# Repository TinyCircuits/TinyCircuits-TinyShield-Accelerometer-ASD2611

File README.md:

# TinyCircuits TinyShield Accelerometer Board
# ASD2611 Rev1

These are the design files for the TinyCircuits ASD2611 Rev 1 PCB.  This is a TinyShield board (Square Version, 20mm x 20mm, or Circular 20mm diameter) that has a Bosch BMA250 accelerometer, local power supply and level shifters to connect between the TinyDuino and the accelerometer. 

Format is in Cadsoft Eagle format - Eagle version 6.2 was used for the original design.

For more infomation on this, check out the product page at Tiny-Circuits.com:  https://tinycircuits.com/collections/sensors/products/accelerometer-tinyshield 

# License:

Design by TinyCircuits.
All design files are released under the Creative Commons Attribution Share-Alike 3.0 License, see the following link for details: http://creativecommons.org/licenses/by-sa/3.0

All text above must be included in any redistribution or derived design

This project uses designs and concepts developed as part of the Arduino project and the LilyPad project.  The TinyCircuits design files themselves (schematics, PCB and libraries) are not directly derived from these works' design files and have been created new, however the concepts and basic architecture behind the TinyDuino and TinyLily products are derived and we thank the hard work of the organizations below for their contributions to open-source hardware:
  
Original Arduino Uno Design by Team Arduino

LilyPad Arduino Design by Leah Buechley and Sparkfun Electronics

Please support the open-source hardware community

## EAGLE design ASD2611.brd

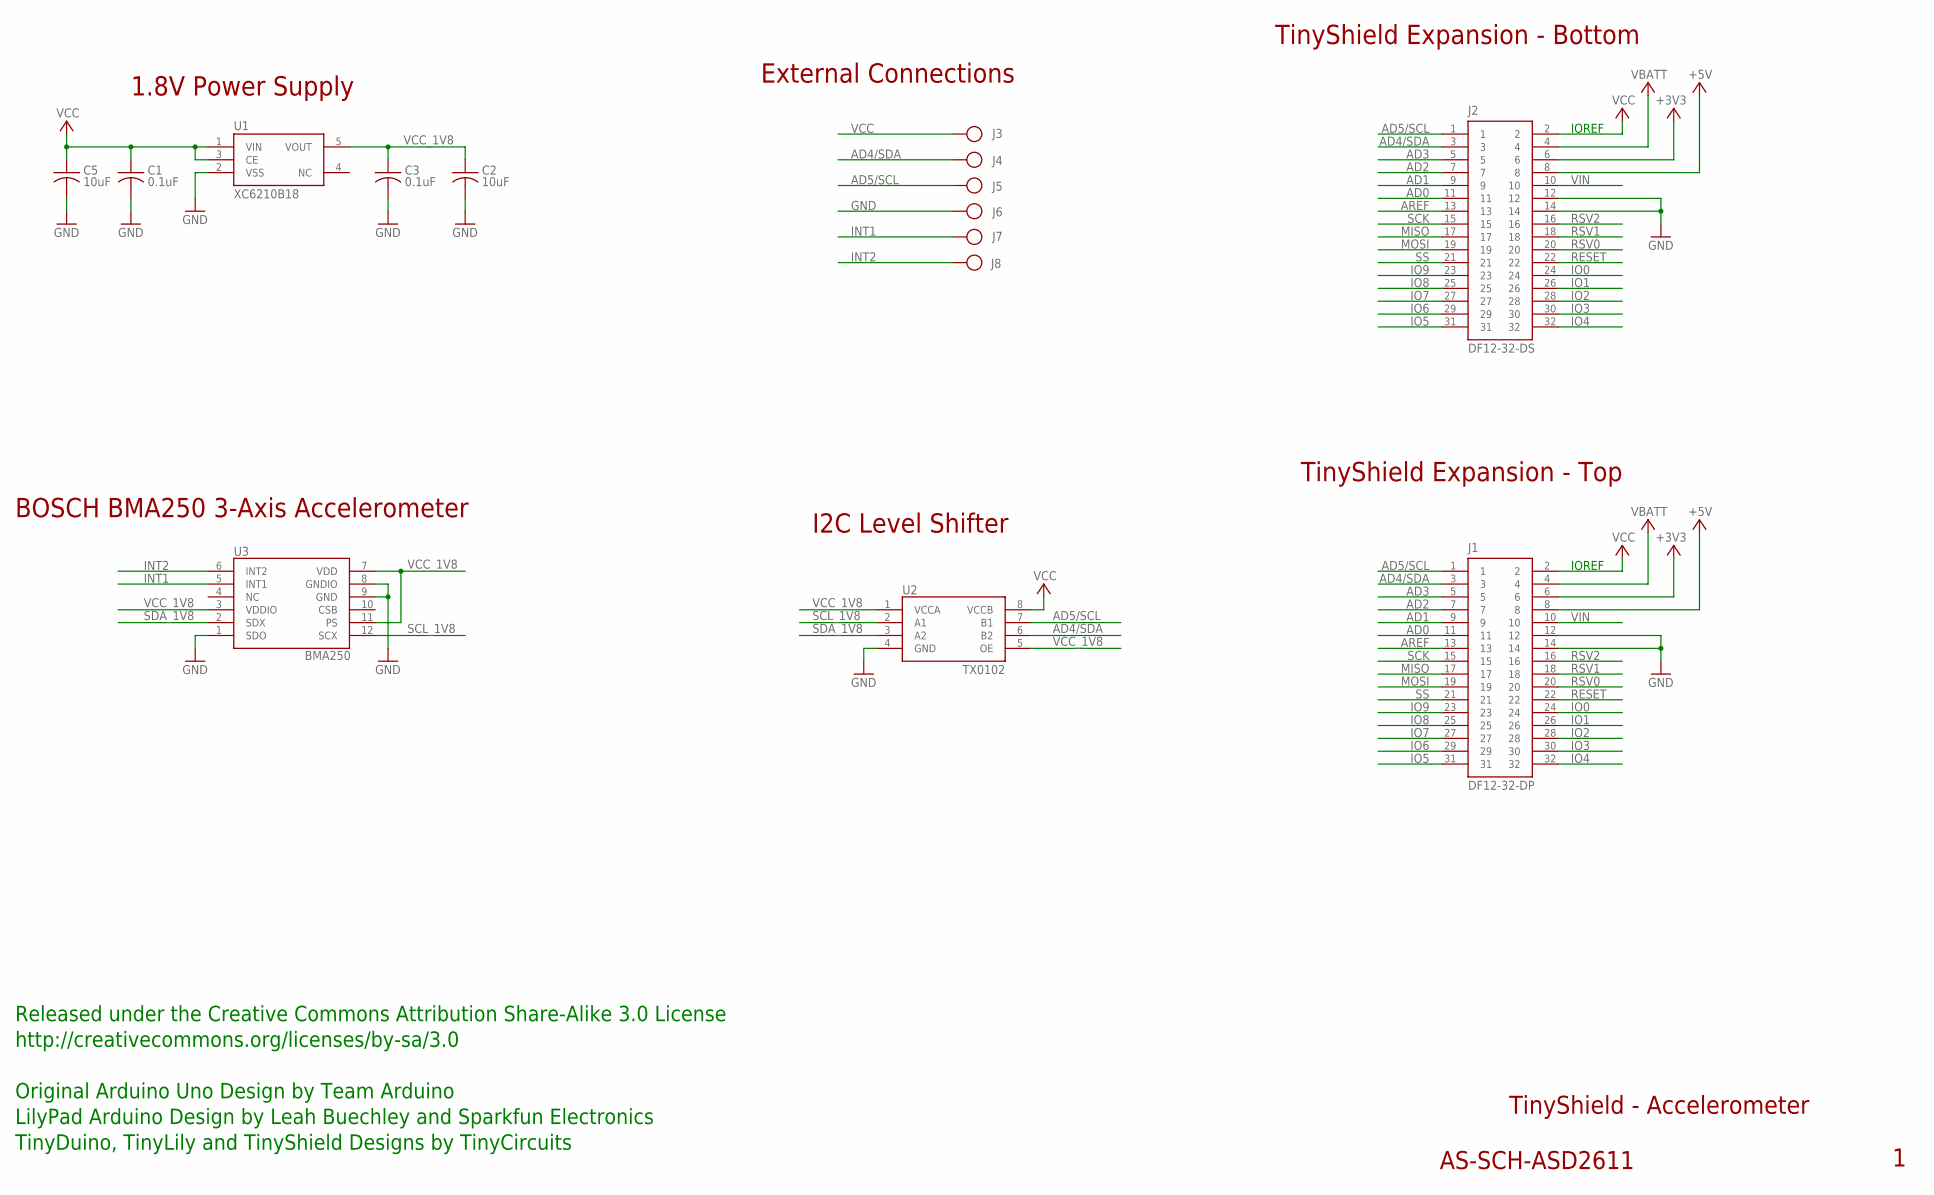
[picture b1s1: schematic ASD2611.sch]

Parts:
C1, C3: 0.1uF; C0402; PARTNO AS-ITM-00008
C2: 10uF; C0805; PARTNO AS-ITM-00045
C5: 10uF; C0805
J1: DF12-32-DP; PARTNO AS-ITM-00015
J2: DF12-32-DS; PARTNO AS-ITM-00012
J3, J4, J5, J6, J7, J8: PIN_1X.1"; 1X.1"
U1: XC6210B18; SOT-25; PARTNO AS-ITM-00075
U2: TX0102; DQE(R-PX2SON-N8)
U3: BMA250; 3-AXIS_ACCELEROMETER

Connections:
+3V3: J1.6, J2.6
+5V: J1.8, J2.8
AD0: J1.11, J2.11
AD1: J1.9, J2.9
AD2: J1.7, J2.7
AD3: J1.5, J2.5
AD4/SDA: J1.3, J2.3, J4.1, U2.6 (B2)
AD5/SCL: J1.1, J2.1, J5.1, U2.7 (B1)
AREF: J1.13, J2.13
GND: C1.2, C2.2, C3.2, C5.2, J1.12, J1.14, J2.12, J2.14, J6.1, U1.2 (VSS), U2.4 (GND), U3.1 (SDO), U3.8 (GNDIO), U3.9 (GND)
INT1: J7.1, U3.5 (INT1)
INT2: J8.1, U3.6 (INT2)
IO0: J1.24, J2.24
IO1: J1.26, J2.26
IO2: J1.28, J2.28
IO3: J1.30, J2.30
IO4: J1.32, J2.32
IO5: J1.31, J2.31
IO6: J1.29, J2.29
IO7: J1.27, J2.27
IO8: J1.25, J2.25
IO9: J1.23, J2.23
MISO: J1.17, J2.17
MOSI: J1.19, J2.19
RESET: J1.22, J2.22
RSV0: J1.20, J2.20
RSV1: J1.18, J2.18
RSV2: J1.16, J2.16
SCK: J1.15, J2.15
SCL_1V8: U2.2 (A1), U3.12 (SCX)
SDA_1V8: U2.3 (A2), U3.2 (SDX)
SS: J1.21, J2.21
VBATT: J1.4, J2.4
VCC: C1.1, C5.1, J1.2, J2.2, J3.1, U1.1 (VIN), U1.3 (CE), U2.8 (VCCB)
VCC_1V8: C2.1, C3.1, U1.5 (VOUT), U2.1 (VCCA), U2.5 (OE), U3.3 (VDDIO), U3.7 (VDD), U3.11 (PS)
VIN: J1.10, J2.10

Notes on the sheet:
TinyShield Expansion - Bottom
TinyShield - Accelerometer
AS-SCH-ASD2611
TinyShield Expansion - Top
IOREF
Released under the Creative Commons Attribution Share-Alike 3.0 License
http://creativecommons.org/licenses/by-sa/3.0
LilyPad Arduino Design by Leah Buechley and Sparkfun Electronics
TinyDuino, TinyLily and TinyShield Designs by TinyCircuits
Original Arduino Uno Design by Team Arduino
External Connections
1.8V Power Supply
I2C Level Shifter
BOSCH BMA250 3-Axis Accelerometer

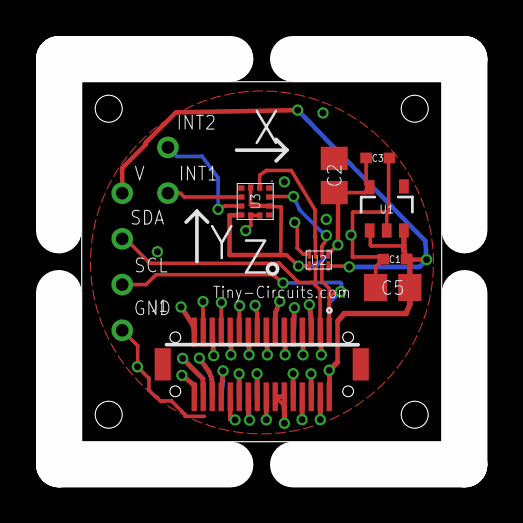
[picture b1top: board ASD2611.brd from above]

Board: 2 copper layers, 20.0 x 20.0 mm, 16 parts (1 on the bottom side), 36 nets.

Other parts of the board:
U$1: DOCFIELD-TINYCIRCUITS-PCB

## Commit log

2014-02-17 Fixed Readme
2014-08-24 Updated Link
2017-03-22 Add sample sketch
2019-01-08 updated comments
2019-01-08 removed example
